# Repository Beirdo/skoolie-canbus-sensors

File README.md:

# skoolie-canbus-sensors
A set of CANBus-attached sensors for the custom CANBus in my skoolie

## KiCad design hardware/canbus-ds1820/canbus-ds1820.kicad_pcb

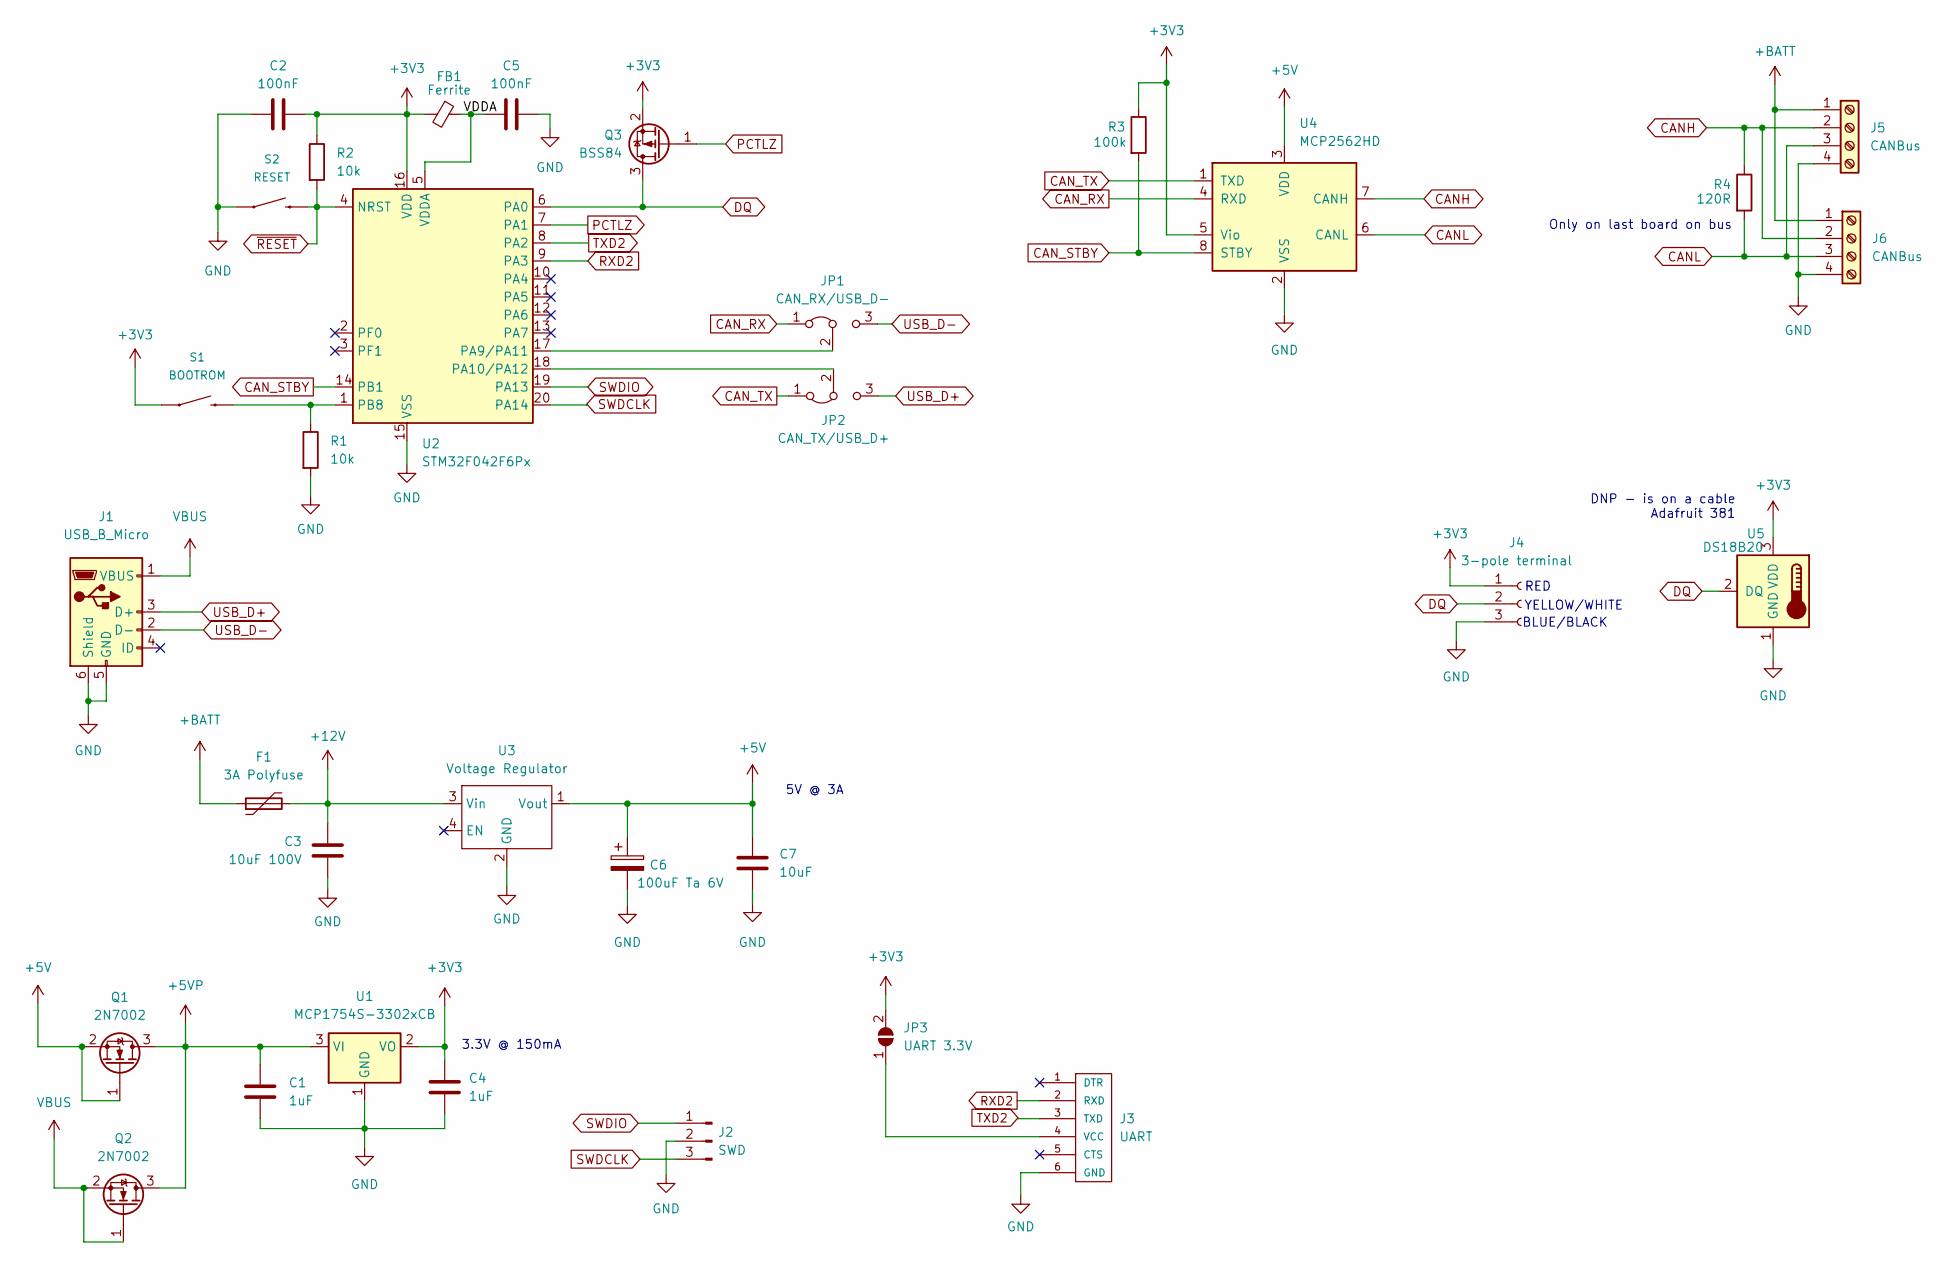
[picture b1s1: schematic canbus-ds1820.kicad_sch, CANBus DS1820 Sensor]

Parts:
C1, C4: 1uF; C_0805_2012Metric_Pad1.18x1.45mm_HandSolder
C2, C5: 100nF; C_0805_2012Metric_Pad1.18x1.45mm_HandSolder
C3: 10uF 100V; C_1210_3225Metric_Pad1.33x2.70mm_HandSolder
C6: 100uF Ta 6V; CP_EIA-3216-10_Kemet-I_Pad1.58x1.35mm_HandSolder
C7: 10uF; C_0805_2012Metric_Pad1.18x1.45mm_HandSolder
F1: 3A Polyfuse; R_1812_4532Metric_Pad1.30x3.40mm_HandSolder; Digikey F2772CT-ND
FB1: Ferrite; L_0805_2012Metric_Pad1.15x1.40mm_HandSolder
J1: USB_B_Micro; USB_Micro-B_Amphenol_10118194_Horizontal
J2: SWD; PinHeader_1x03_P2.54mm_Vertical
J3: UART; FTDI-TARGET
J4: 3-pole terminal; TerminalBlock_TE_282834-3_1x03_P2.54mm_Horizontal
J5, J6: CANBus; TerminalBlock_TE_282834-4_1x04_P2.54mm_Horizontal
JP1: CAN_RX/USB_D-; PinHeader_1x03_P2.54mm_Vertical
JP2: CAN_TX/USB_D+; PinHeader_1x03_P2.54mm_Vertical
JP3: UART 3.3V; SolderJumper-2_P1.3mm_Open_TrianglePad1.0x1.5mm
Q1, Q2: 2N7002; SOT-23
Q3: BSS84; SOT-23
R1, R2: 10k; R_0805_2012Metric_Pad1.20x1.40mm_HandSolder
R3: 100k; R_0805_2012Metric_Pad1.20x1.40mm_HandSolder
R4: 120R; R_0805_2012Metric_Pad1.20x1.40mm_HandSolder
S1: BOOTROM; TACTILE_SWITCH_PTH_6.0MM
S2: RESET; TACTILE_SWITCH_PTH_6.0MM
U1: MCP1754S-3302xCB; SOT-23
U2: STM32F042F6Px; TSSOP-20_4.4x6.5mm_P0.65mm
U3: Voltage Regulator; Switching_Regulator_Module
U4: MCP2562HD; SOIC-8_3.9x4.9mm_P1.27mm
U5: DS18B20; TO-92_Inline

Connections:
+3V3: C2.2, C4.1, FB1.2, J4.1, JP3.2 (B), Q3.2 (S), R2.1, R3.1, S1.1, U1.2 (VO), U2.16 (VDD), U4.5 (Vio), U5.3 (VDD)
+5V: C6.1, C7.1, Q1.1 (G), Q1.2 (S), U3.1 (Vout), U4.3 (VDD)
+5VP: C1.1, Q1.3 (D), Q2.3 (D), U1.3 (VI)
+12V: C3.1, F1.2, U3.3 (Vin)
+BATT: F1.1, J5.1, J6.1
/VDDA: C5.1, FB1.1, U2.5 (VDDA)
CANH: J5.2, J6.2, R4.1, U4.7 (CANH)
CANL: J5.3, J6.3, R4.2, U4.6 (CANL)
CAN_RX: JP1.1 (A), U4.4 (RXD)
CAN_STBY: R3.2, U2.14 (PB1), U4.8 (STBY)
CAN_TX: JP2.1 (A), U4.1 (TXD)
DQ: J4.2, Q3.3 (D), U2.6 (PA0), U5.2 (DQ)
GND: C1.2, C2.1, C3.2, C4.2, C5.2, C6.2, C7.2, J1.5 (GND), J1.6 (Shield), J2.2, J3.6 (GND), J4.3, J5.4, J6.4, R1.2, S2.1, U1.1 (GND), U2.15 (VSS), U3.2 (GND), U4.2 (VSS), U5.1 (GND)
unnamed: J3.4 (VCC), JP3.1 (A)
unnamed: JP1.2 (C), U2.17 (PA9/PA11)
unnamed: JP2.2 (C), U2.18 (PA10/PA12)
unnamed: R1.1, S1.3 (2), U2.1 (PB8)
PCTLZ: Q3.1 (G), U2.7 (PA1)
RXD2: J3.2 (RXD), U2.9 (PA3)
SWDCLK: J2.3, U2.20 (PA14)
SWDIO: J2.1, U2.19 (PA13)
TXD2: J3.3 (TXD), U2.8 (PA2)
USB_D+: J1.3 (D+), JP2.3 (B)
USB_D-: J1.2 (D-), JP1.3 (B)
VBUS: J1.1 (VBUS), Q2.1 (G), Q2.2 (S)
~RESET: R2.2, S2.3 (2), U2.4 (NRST)

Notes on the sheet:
5V @ 3A
Only on last board on bus
BLUE/BLACK
YELLOW/WHITE
RED
DNP - is on a cable Adafruit 381
3.3V @ 150mA

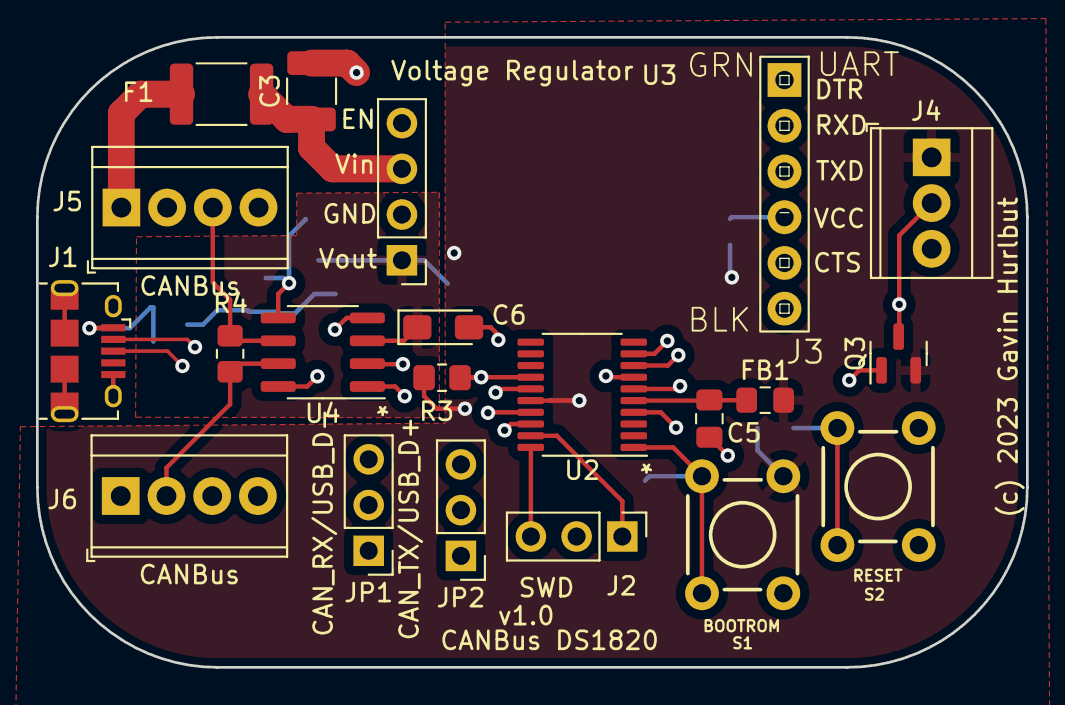
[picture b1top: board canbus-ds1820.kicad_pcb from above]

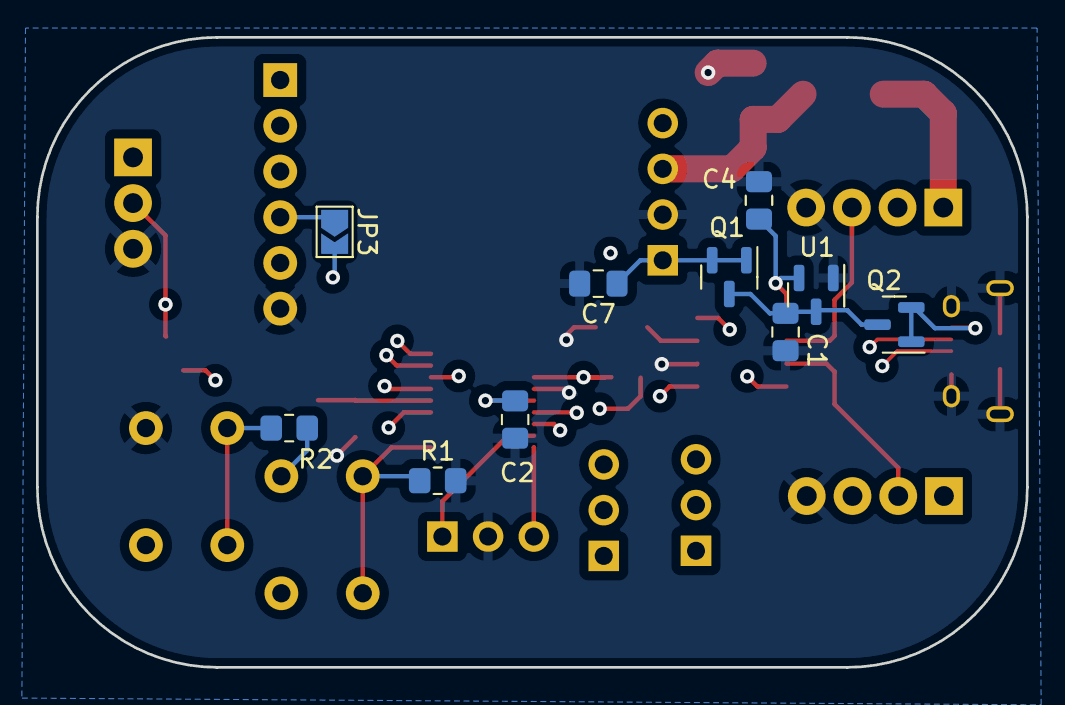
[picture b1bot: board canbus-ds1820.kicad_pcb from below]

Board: 4 copper layers, 55.0 x 35.0 mm, 32 parts (10 on the bottom side), 26 nets.

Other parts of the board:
BOARD: Altoid-Board-Outline

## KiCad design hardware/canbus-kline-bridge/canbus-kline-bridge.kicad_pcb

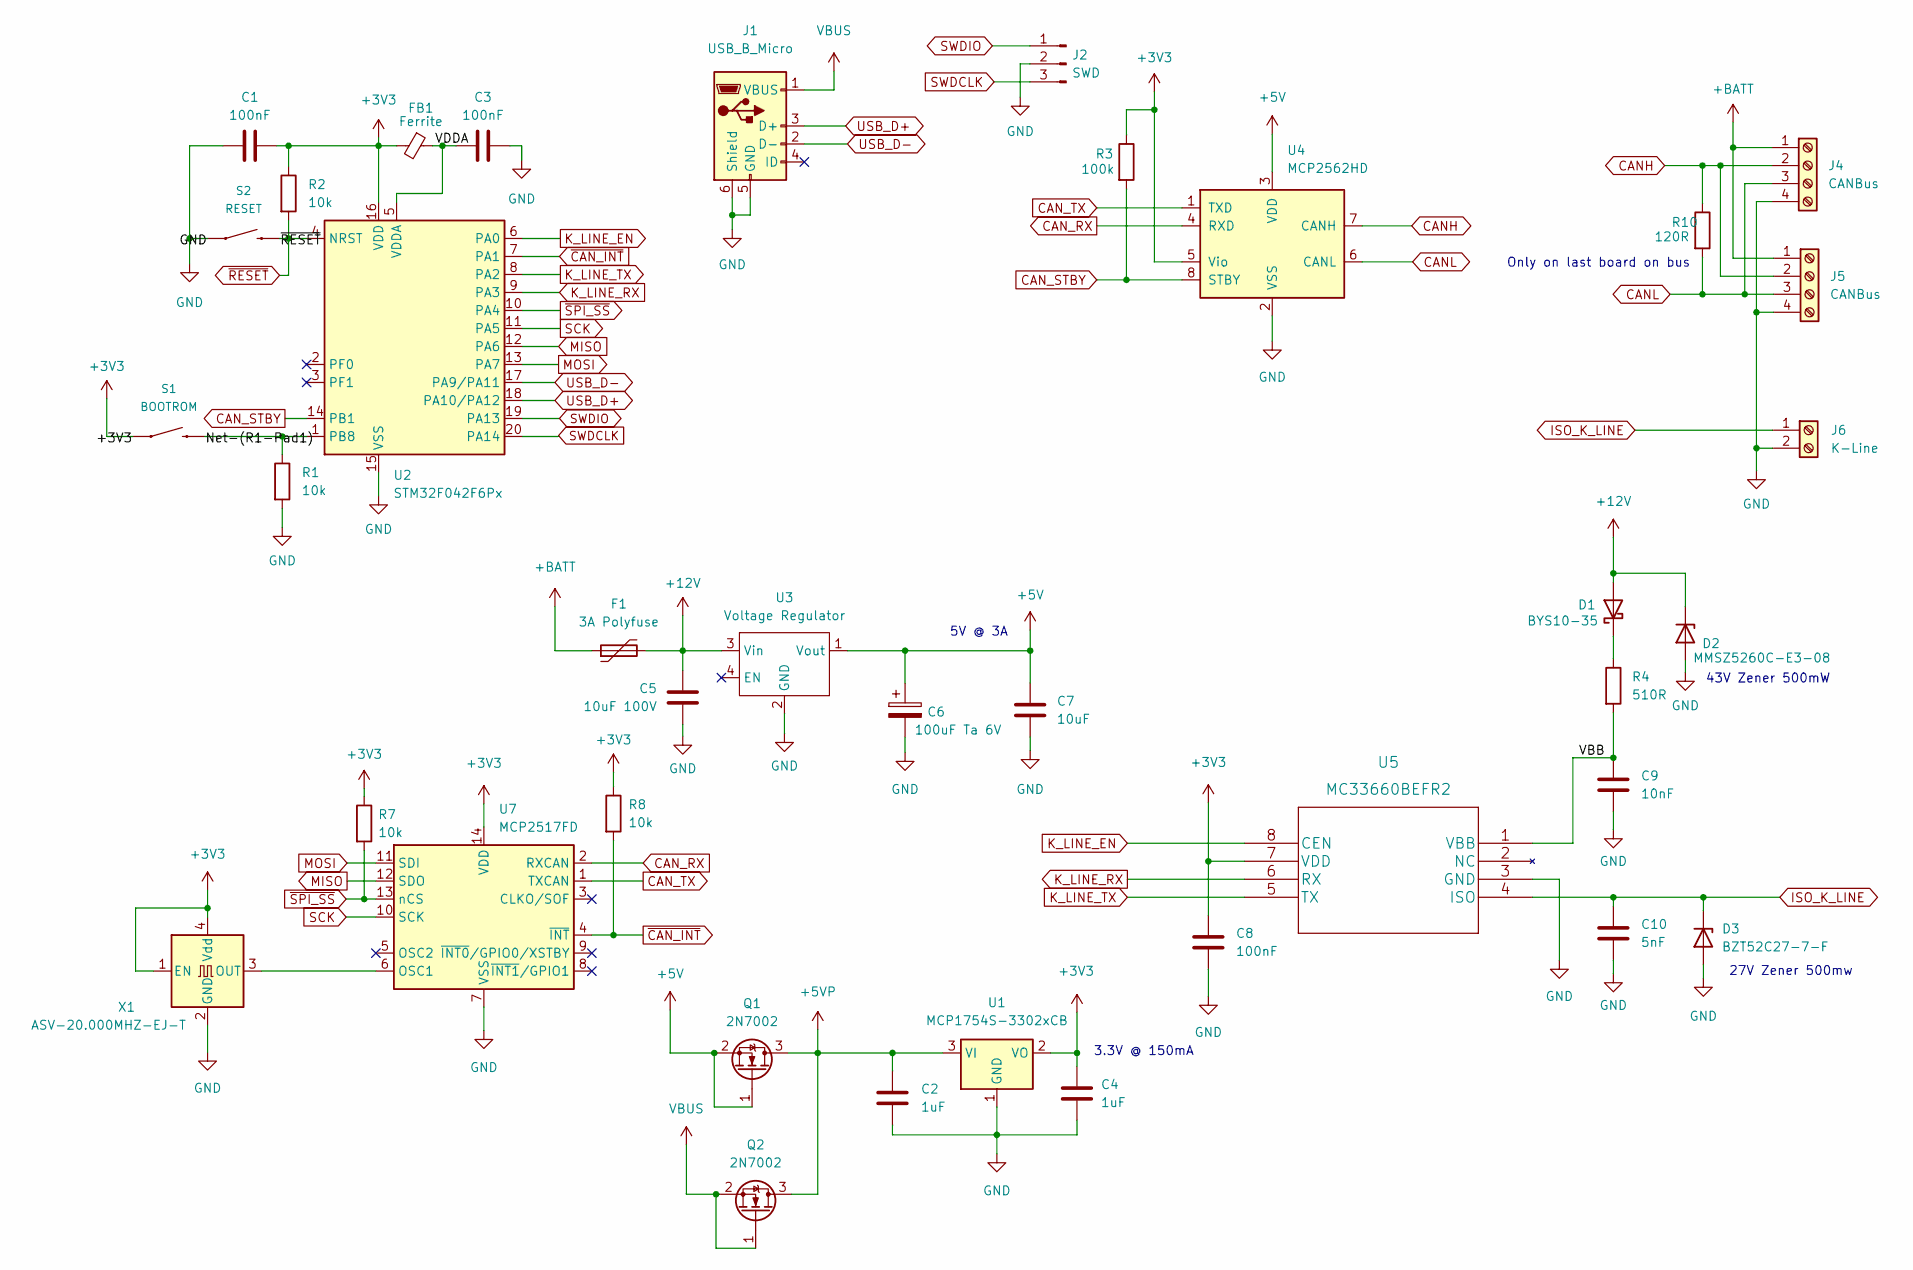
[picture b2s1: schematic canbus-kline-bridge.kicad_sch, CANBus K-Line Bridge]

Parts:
C1, C3, C8: 100nF; C_0805_2012Metric_Pad1.18x1.45mm_HandSolder
C2, C4: 1uF; C_0805_2012Metric_Pad1.18x1.45mm_HandSolder
C5: 10uF 100V; C_1210_3225Metric_Pad1.33x2.70mm_HandSolder
C6: 100uF Ta 6V; CP_EIA-3216-10_Kemet-I_Pad1.58x1.35mm_HandSolder
C7: 10uF; C_0805_2012Metric_Pad1.18x1.45mm_HandSolder
C9: 10nF; C_0805_2012Metric_Pad1.18x1.45mm_HandSolder
C10: 5nF; C_0805_2012Metric_Pad1.18x1.45mm_HandSolder
D1: BYS10-35; D_SMA_Handsoldering
D2: MMSZ5260C-E3-08; D_SOD-123
D3: BZT52C27-7-F; D_SOD-123
F1: 3A Polyfuse; R_1812_4532Metric_Pad1.30x3.40mm_HandSolder; Digikey F2772CT-ND
FB1: Ferrite; L_0805_2012Metric_Pad1.15x1.40mm_HandSolder
J1: USB_B_Micro; USB_Micro-B_Amphenol_10118194_Horizontal
J2: SWD; PinHeader_1x03_P2.54mm_Vertical
J4, J5: CANBus; TerminalBlock_TE_282834-4_1x04_P2.54mm_Horizontal
J6: K-Line; TerminalBlock_TE_282834-2_1x02_P2.54mm_Horizontal
Q1, Q2: 2N7002; SOT-23
R1, R2, R7, R8: 10k; R_0805_2012Metric_Pad1.20x1.40mm_HandSolder
R3: 100k; R_0805_2012Metric_Pad1.20x1.40mm_HandSolder
R4: 510R; R_0805_2012Metric_Pad1.20x1.40mm_HandSolder
R10: 120R; R_0805_2012Metric_Pad1.20x1.40mm_HandSolder
S1: BOOTROM; TACTILE_SWITCH_PTH_6.0MM
S2: RESET; TACTILE_SWITCH_PTH_6.0MM
U1: MCP1754S-3302xCB; SOT-23
U2: STM32F042F6Px; TSSOP-20_4.4x6.5mm_P0.65mm
U3: Voltage Regulator; Switching_Regulator_Module
U4: MCP2562HD; SOIC-8_3.9x4.9mm_P1.27mm
U5: MC33660BEFR2
U7: MCP2517FD; SOIC-14_3.9x8.7mm_P1.27mm
X1: ASV-20.000MHZ-EJ-T; Oscillator_SMD_Abracon_ASV-4Pin_7.0x5.1mm

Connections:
+3V3: C1.2, C4.1, C8.1, FB1.2, R2.1, R3.1, R7.1, R8.1, S1.1, S1.2 (1), U1.2 (VO), U2.16 (VDD), U4.5 (Vio), U5.7 (VDD), U7.14 (VDD), X1.1 (EN), X1.4 (Vdd)
+5V: C6.1, C7.1, Q1.1 (G), Q1.2 (S), U3.1 (Vout), U4.3 (VDD)
+5VP: C2.1, Q1.3 (D), Q2.3 (D), U1.3 (VI)
+12V: C5.1, D1.2 (A), D2.1 (K), F1.2, U3.3 (Vin)
+BATT: F1.1, J4.1, J5.1
/Net-(R1-Pad1): S1.4 (2)
/VBB: C9.1, R4.2, U5.1 (VBB)
/VDDA: C3.1, FB1.1, U2.5 (VDDA)
CANH: J4.2, J5.2, R10.1, U4.7 (CANH)
CANL: J4.3, J5.3, R10.2, U4.6 (CANL)
CAN_RX: U4.4 (RXD), U7.2 (RXCAN)
CAN_STBY: R3.2, U2.14 (PB1), U4.8 (STBY)
CAN_TX: U4.1 (TXD), U7.1 (TXCAN)
GND: C1.1, C2.2, C3.2, C4.2, C5.2, C6.2, C7.2, C8.2, C9.2, C10.2, D2.2 (A), D3.2 (A), J1.5 (GND), J1.6 (Shield), J2.2, J4.4, J5.4, J6.2, R1.2, S2.1, S2.2 (1), U1.1 (GND), U2.15 (VSS), U3.2 (GND), U4.2 (VSS), U5.3 (GND), U7.7 (VSS), X1.2 (GND)
ISO_K_LINE: C10.1, D3.1 (K), J6.1, U5.4 (ISO)
K_LINE_EN: U2.6 (PA0), U5.8 (CEN)
K_LINE_RX: U2.9 (PA3), U5.6 (RX)
K_LINE_TX: U2.8 (PA2), U5.5 (TX)
MISO: U2.12 (PA6), U7.12 (SDO)
MOSI: U2.13 (PA7), U7.11 (SDI)
unnamed: D1.1 (K), R4.1
unnamed: R1.1, S1.3 (2), U2.1 (PB8)
unnamed: U7.6 (OSC1), X1.3 (OUT)
SCK: U2.11 (PA5), U7.10 (SCK)
SWDCLK: J2.3, U2.20 (PA14)
SWDIO: J2.1, U2.19 (PA13)
USB_D+: J1.3 (D+), U2.18 (PA10/PA12)
USB_D-: J1.2 (D-), U2.17 (PA9/PA11)
VBUS: J1.1 (VBUS), Q2.1 (G), Q2.2 (S)
~CAN_INT: R8.2, U2.7 (PA1), U7.4 (~INT)
~RESET: R2.2, S2.3 (2), S2.4 (2), U2.4 (NRST)
~SPI_SS: R7.2, U2.10 (PA4), U7.13 (nCS)

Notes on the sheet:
5V @ 3A
Only on last board on bus
27V Zener 500mw
3.3V @ 150mA
43V Zener 500mW

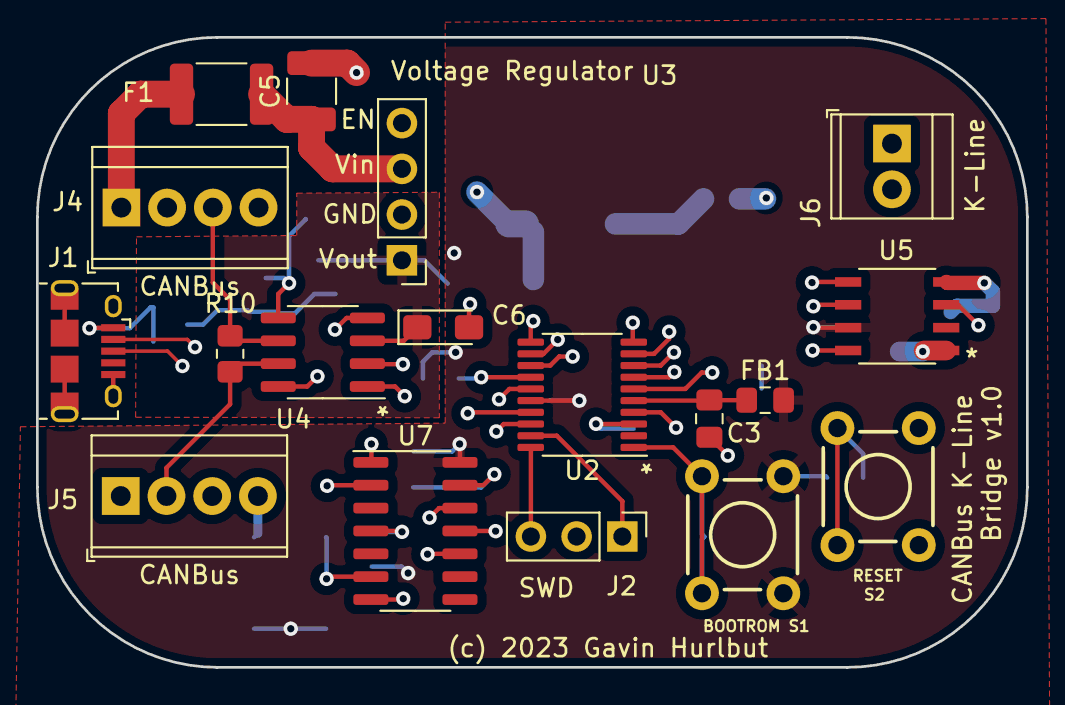
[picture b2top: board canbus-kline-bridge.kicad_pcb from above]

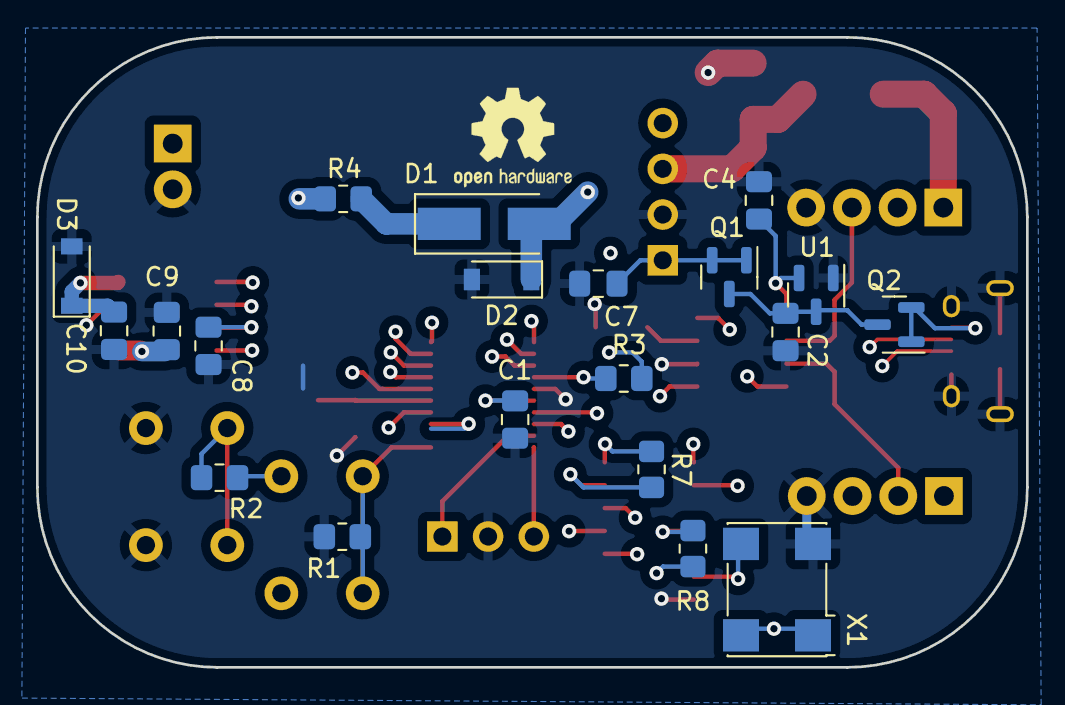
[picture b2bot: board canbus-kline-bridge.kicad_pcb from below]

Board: 4 copper layers, 55.0 x 35.0 mm, 39 parts (20 on the bottom side), 31 nets.

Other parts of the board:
BOARD: Altoid-Board-Outline

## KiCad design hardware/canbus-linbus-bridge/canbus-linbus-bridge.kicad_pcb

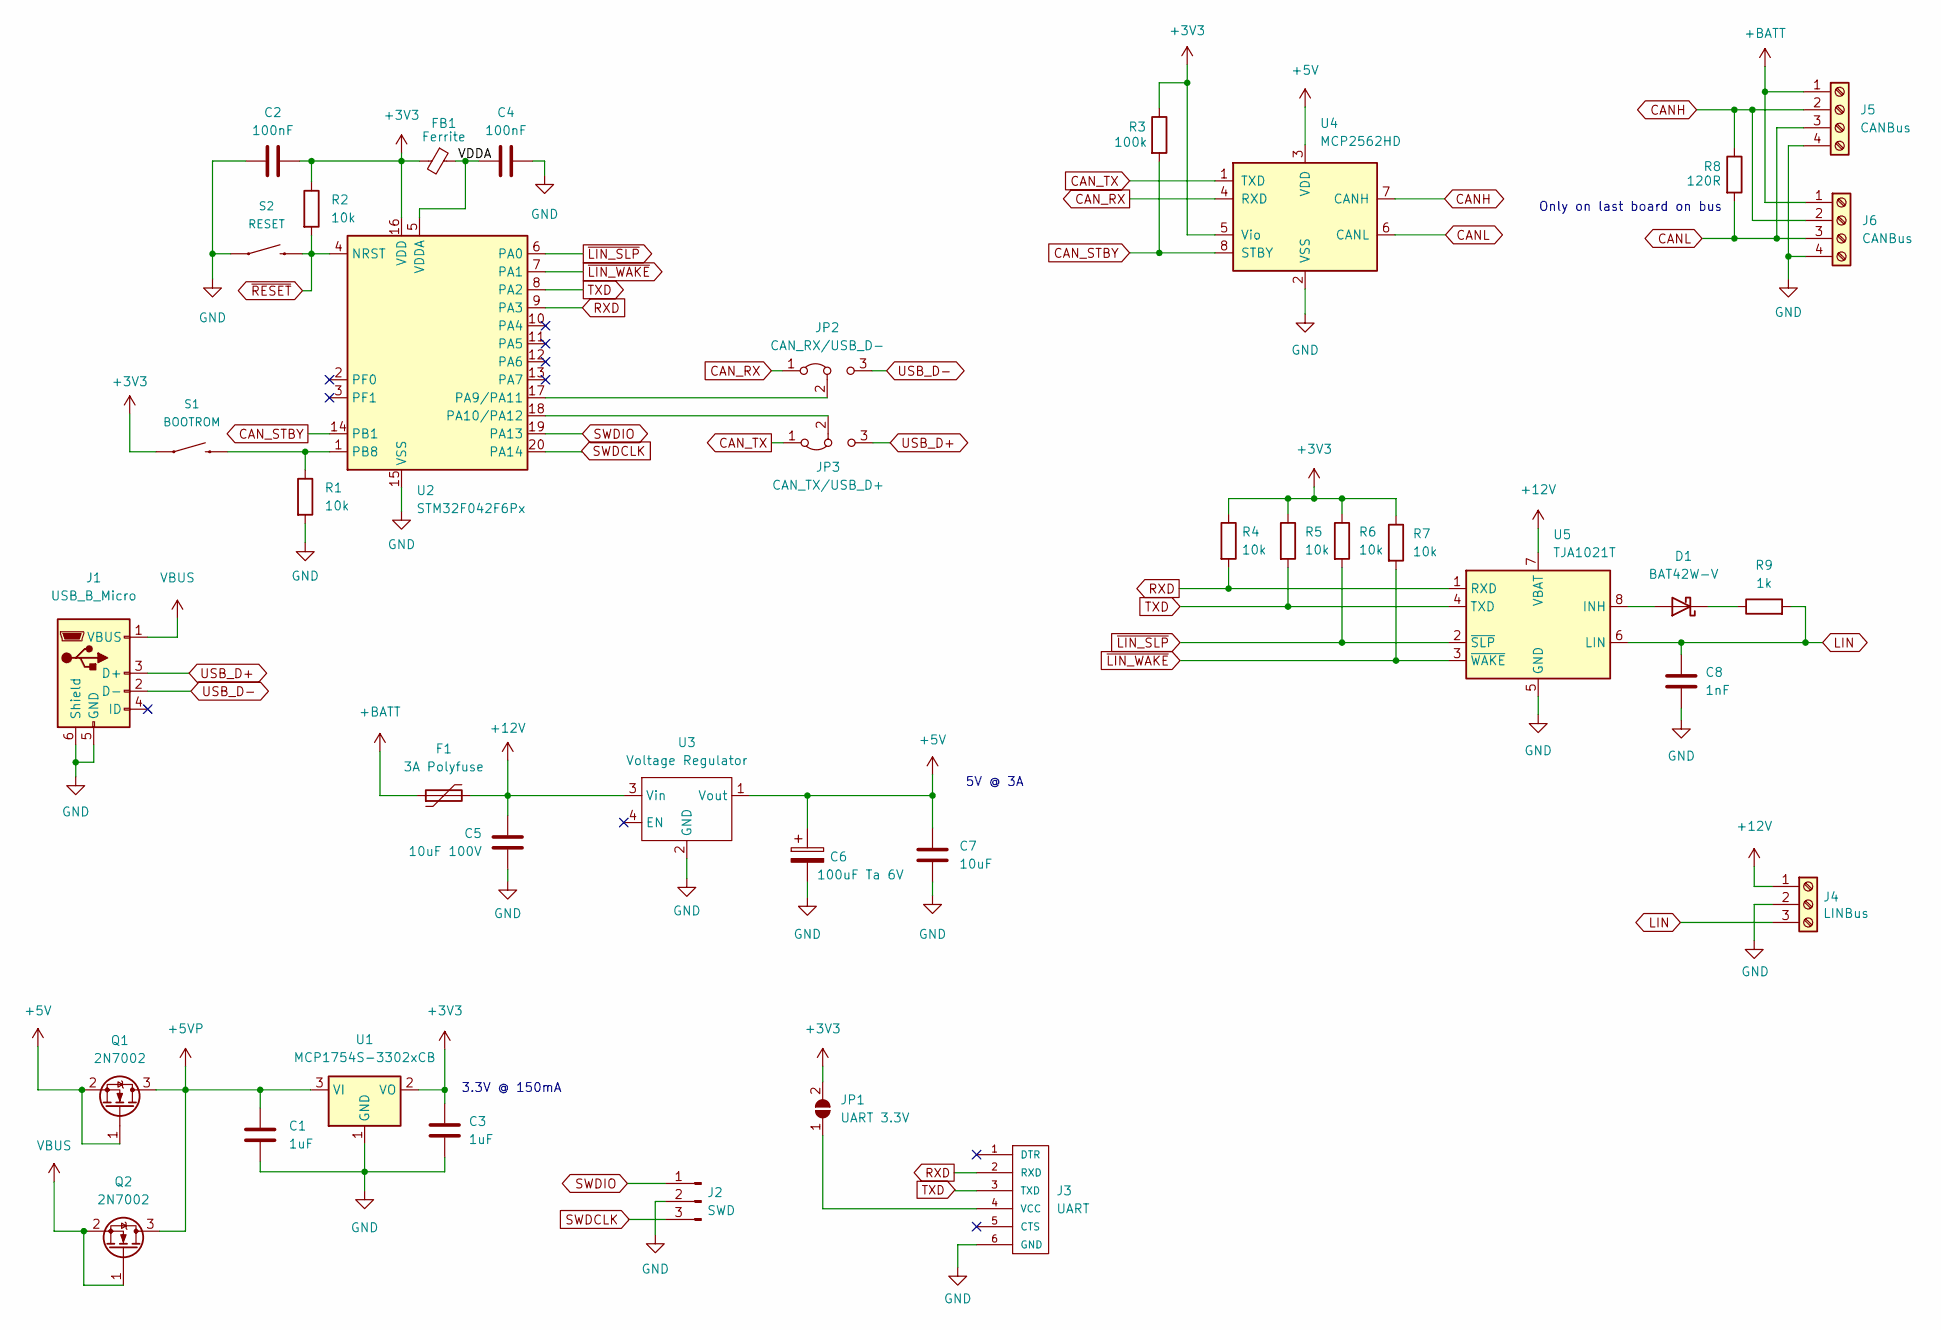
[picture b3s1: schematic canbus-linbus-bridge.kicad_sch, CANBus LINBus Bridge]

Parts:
C1, C3: 1uF; C_0805_2012Metric_Pad1.18x1.45mm_HandSolder
C2, C4: 100nF; C_0805_2012Metric_Pad1.18x1.45mm_HandSolder
C5: 10uF 100V; C_1210_3225Metric_Pad1.33x2.70mm_HandSolder
C6: 100uF Ta 6V; CP_EIA-3216-10_Kemet-I_Pad1.58x1.35mm_HandSolder
C7: 10uF; C_0805_2012Metric_Pad1.18x1.45mm_HandSolder
C8: 1nF; C_0805_2012Metric_Pad1.18x1.45mm_HandSolder
D1: BAT42W-V; D_SOD-123
F1: 3A Polyfuse; R_1812_4532Metric_Pad1.30x3.40mm_HandSolder; Digikey F2772CT-ND
FB1: Ferrite; L_0805_2012Metric_Pad1.15x1.40mm_HandSolder
J1: USB_B_Micro; USB_Micro-B_Amphenol_10118194_Horizontal
J2: SWD; PinHeader_1x03_P2.54mm_Vertical
J3: UART; FTDI-TARGET
J4: LINBus; TerminalBlock_TE_282834-3_1x03_P2.54mm_Horizontal
J5, J6: CANBus; TerminalBlock_TE_282834-4_1x04_P2.54mm_Horizontal
JP1: UART 3.3V; SolderJumper-2_P1.3mm_Open_TrianglePad1.0x1.5mm
JP2: CAN_RX/USB_D-; PinHeader_1x03_P2.54mm_Vertical
JP3: CAN_TX/USB_D+; PinHeader_1x03_P2.54mm_Vertical
Q1, Q2: 2N7002; SOT-23
R1, R2, R4, R5, R6, R7: 10k; R_0805_2012Metric_Pad1.20x1.40mm_HandSolder
R3: 100k; R_0805_2012Metric_Pad1.20x1.40mm_HandSolder
R8: 120R; R_0805_2012Metric_Pad1.20x1.40mm_HandSolder
R9: 1k; R_0805_2012Metric_Pad1.20x1.40mm_HandSolder
S1: BOOTROM; TACTILE_SWITCH_PTH_6.0MM
S2: RESET; TACTILE_SWITCH_PTH_6.0MM
U1: MCP1754S-3302xCB; SOT-23
U2: STM32F042F6Px; TSSOP-20_4.4x6.5mm_P0.65mm
U3: Voltage Regulator; Switching_Regulator_Module
U4: MCP2562HD; SOIC-8_3.9x4.9mm_P1.27mm
U5: TJA1021T; SOIC-8_3.9x4.9mm_P1.27mm

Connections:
+3V3: C2.2, C3.1, FB1.2, JP1.2 (B), R2.1, R3.1, R4.1, R5.1, R6.1, R7.1, S1.1, U1.2 (VO), U2.16 (VDD), U4.5 (Vio)
+5V: C6.1, C7.1, Q1.1 (G), Q1.2 (S), U3.1 (Vout), U4.3 (VDD)
+5VP: C1.1, Q1.3 (D), Q2.3 (D), U1.3 (VI)
+12V: C5.1, F1.2, J4.1, U3.3 (Vin), U5.7 (VBAT)
+BATT: F1.1, J5.1, J6.1
/VDDA: C4.1, FB1.1, U2.5 (VDDA)
CANH: J5.2, J6.2, R8.1, U4.7 (CANH)
CANL: J5.3, J6.3, R8.2, U4.6 (CANL)
CAN_RX: JP2.1 (A), U4.4 (RXD)
CAN_STBY: R3.2, U2.14 (PB1), U4.8 (STBY)
CAN_TX: JP3.1 (A), U4.1 (TXD)
GND: C1.2, C2.1, C3.2, C4.2, C5.2, C6.2, C7.2, C8.2, J1.5 (GND), J1.6 (Shield), J2.2, J3.6 (GND), J4.2, J5.4, J6.4, R1.2, S2.1, U1.1 (GND), U2.15 (VSS), U3.2 (GND), U4.2 (VSS), U5.5 (GND)
LIN: C8.1, J4.3, R9.2, U5.6 (LIN)
unnamed: D1.1 (K), R9.1
unnamed: D1.2 (A), U5.8 (INH)
unnamed: J3.4 (VCC), JP1.1 (A)
unnamed: JP2.2 (C), U2.17 (PA9/PA11)
unnamed: JP3.2 (C), U2.18 (PA10/PA12)
unnamed: R1.1, S1.3 (2), U2.1 (PB8)
RXD: J3.2 (RXD), R4.2, U2.9 (PA3), U5.1 (RXD)
SWDCLK: J2.3, U2.20 (PA14)
SWDIO: J2.1, U2.19 (PA13)
TXD: J3.3 (TXD), R5.2, U2.8 (PA2), U5.4 (TXD)
USB_D+: J1.3 (D+), JP3.3 (B)
USB_D-: J1.2 (D-), JP2.3 (B)
VBUS: J1.1 (VBUS), Q2.1 (G), Q2.2 (S)
~LIN_SLP: R6.2, U2.6 (PA0), U5.2 (~SLP)
~LIN_WAKE: R7.2, U2.7 (PA1), U5.3 (~WAKE)
~RESET: R2.2, S2.3 (2), U2.4 (NRST)

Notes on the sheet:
5V @ 3A
Only on last board on bus
3.3V @ 150mA

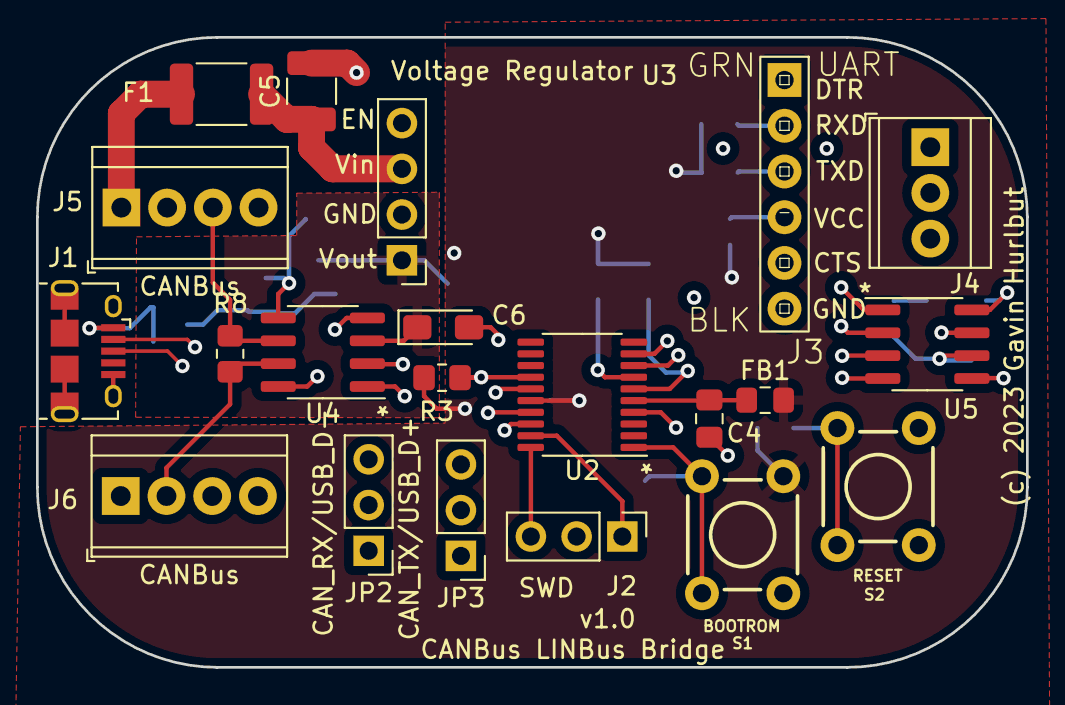
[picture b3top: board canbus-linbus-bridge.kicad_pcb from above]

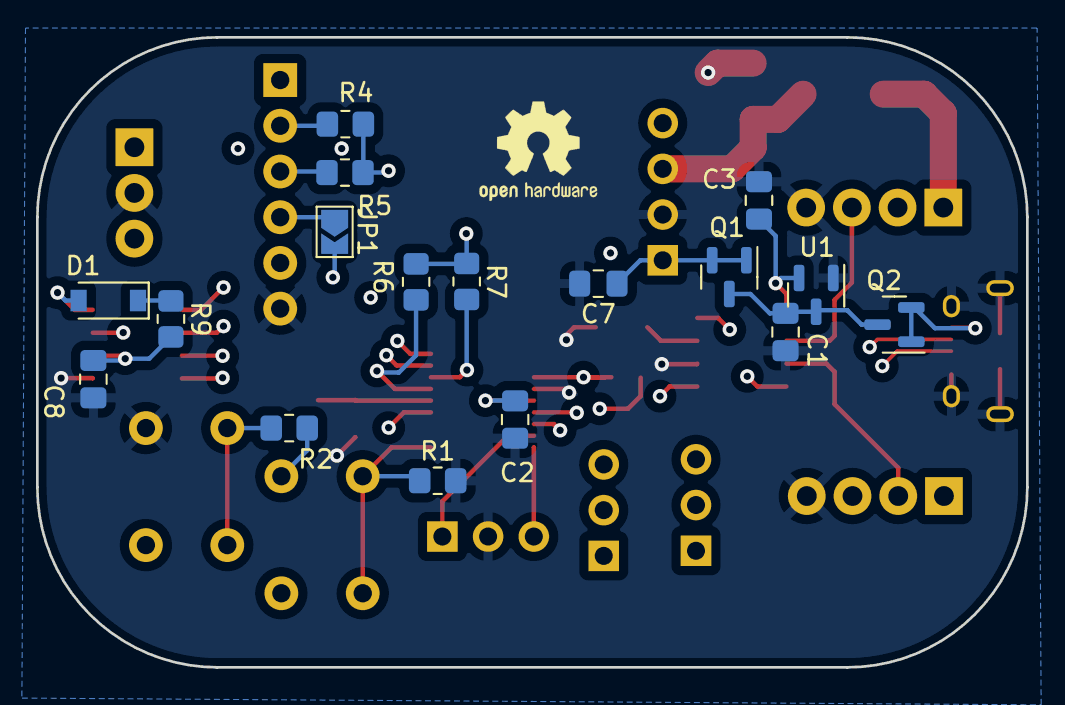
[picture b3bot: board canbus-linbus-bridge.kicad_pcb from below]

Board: 4 copper layers, 55.0 x 35.0 mm, 39 parts (17 on the bottom side), 29 nets.

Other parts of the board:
BOARD: Altoid-Board-Outline

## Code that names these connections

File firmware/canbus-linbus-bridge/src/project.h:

#ifndef __project_h_
#define __project_h_

#include <Beirdo-Utilities.h>

#include "linbus_bridge.h"

#define PIN_LIN_SLP           0   // PA_0
#define PIN_LIN_WAKE          1   // PA_1
#define PIN_USART2_TX         2   // PA_2
#define PIN_USART2_RX         3   // PA_3
#define PIN_SWDIO             10  // PA_13
#define PIN_SWDCLK            11  // PA_14
#define PIN_CAN_EN            12  // PB_1
#define PIN_BOOTROM_SEL       13  // PB_8
#define PIN_CAN_RX            16  // PA_11_R
#define PIN_CAN_TX            17  // PA_12_R


extern LINBusBridge linbusBridge;

#endif

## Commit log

2023-03-01 Moved in from old repo
2023-03-01 Spin off a board for the linbus bridge
2023-03-01 Add linbus bridge code, board (not compiling yet)
2023-03-01 Get the linbus bridge compiling
2023-03-01 Allow for non-2 byte registers
2023-03-02 Fix the filter masks (oops)
2023-03-02 Whitespace fixes
2023-03-03 Add more linbus mappings, rework the bridge code
2023-03-04 Added a metric butt-ton of sensors. I think that's all of em.
2023-03-05 Got canbus-de1820 up in PlatformIO
2023-03-05 Moved canbus-gpios to PlatformIO
2023-03-05 Moved canbus-linbus-bridge to PlatformIO
2023-03-05 Moved canbus-thermistor over to PlatformIO
2023-03-05 Moved canbus-thermocouple over to PlatformIO
2023-03-05 Add new canbus-kline-bridge board.
2023-03-05 Starting the firmware for the canbus-kline-bridge
2023-03-05 Rename the default env to ststm32
2023-03-06 Working on the kline bridge a bit more
2023-03-06 Plumbed out the kline over canbus code
2023-03-06 Implemented DS1820 directly, no DS2482
2023-03-06 Added the virtualization of logging in STM32-CAN
2023-03-06 Stop using *.ino.
2023-03-06 Move over to using CANBUS_ID_WBUS
2023-03-07 Added custom break handling via a custom STSTM32 framework
2023-03-07 Move canbus-ds1820 to using lib_deps
2023-03-07 Move canbus-gpios to lib_deps
2023-03-07 Move canbus-kline-bridge to lib_deps
2023-03-07 Move canbus-linbus-bridge to lib_deps
2023-03-07 Move canbus-thermistor to lib_deps
2023-03-07 Moved canbus-thermocouple to lib_deps

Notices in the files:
hardware/canbus-ds1820/canbus-ds1820.kicad_pcb:
(c) 2023 Gavin Hurlbut
